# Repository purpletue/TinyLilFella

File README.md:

# TinyLilFella – An Microscopic STM32 Board

### My Tiny Glowing Submission to Hack Club Stardance

---

## Screenshots

*Gotta love them pictures.*

---

## What is this?

An absolutely microscopic (metaphorically... and literally, being under 0.8 cm³) microcontroller board based on the **STM32C071**.

The name is fully deserved. It packs power, an RGB LED, and 6 breakout GPIO lines into a tiny USB dongle form factor!

### Features:

* **STM32C071 Microcontroller** – Arm Cortex-M0+ running up to 48 MHz.
* **Dongle Form Factor** – Plugs straight in like a USB key.
* **Tactile Reset Button** – Dedicated hardware reset driving `NRST` low.
* **Onboard RGB LED** – Connected to PWM-capable pins for status/vibes.
* **10-Pin Header Breakout** – Power rails and 6 general-purpose GPIOs for compact integration.
* **Bootloader button** - The way to program the board.
* **Programmable button** - Just a simple button sitting at PA6, you can program it to do anything!

---

### Repository index:

* root - where [LICENSE](https://github.com/purpletue/TinyLilFella/blob/main/LICENSE) and this document live.
* root/files - where the main files are. like the [project file](https://github.com/purpletue/TinyLilFella/blob/main/files/TinyLilFucker.kicad_pro), [schematic](https://github.com/purpletue/TinyLilFella/blob/main/files/TinyLilFucker.kicad_sch), and [PCB file](https://github.com/purpletue/TinyLilFella/blob/main/files/TinyLilFucker.kicad_pcb) are.
* root/files/production - where the files necessary for production of the PCB are, such as [gerbers.zip](https://github.com/purpletue/TinyLilFella/blob/main/files/production/gerbers.zip) and the [Bill of Materials](https://github.com/purpletue/TinyLilFella/blob/main/files/production/BOM.csv) live.
* root/examples - where code examples such as [LED showcase](https://github.com/purpletue/TinyLilFella/blob/main/examples/led.cpp) are.

## How It Works:

The board takes 5V power directly via standard USB-A / VBUS line. An onboard low-dropout (LDO) regulator steps that down to a clean 3.3V logic level to power the main STM32 MCU and external low-power sensors.

The 10-pin header brings out 6 direct GPIO lines (`PA0` through `PA5`) alongside system ground and power rails for easy modular hooking up.

---

## Why?

Built for **Hack Club Stardance**! I wanted to see how far I could shrink down a functional, highly integrated ARM Cortex dev board into a minimal 1.5 cm³ footprint.

---

## Technical Specifications

| Feature | Details |
| --- | --- |
| **Microcontroller** | STM32C071 (Arm Cortex-M0+, up to 48 MHz) |
| **Form Factor** | Dongle-sized (< 0.8 cm³) |
| **Input Voltage** | 5V via USB-A / VBUS pin |
| **Logic Level** | 3.3V (Onboard LDO regulator) |
| **Pin Count** | 10 pins total (6 GPIO, 2x GND, 1x 3.3V, 1x 5V/VBUS) |
| **Onboard Controls** | Tactile Reset Pushbutton |
| **Indicators** | Onboard RGB LED for programming + an extra power indicator. |

---

## Pinout Mapping

| Pin | Function | Type | Description |
| --- | --- | --- | --- |
| **1** | `GND` | Power | System Ground |
| **2** | `GND` | Power | System Ground |
| **3** | `3V3` | Power | Regulated 3.3V Output |
| **4** | `5V / VBUS` | Power | USB Power Input / 5V Bus |
| **5** | `GPIO 1` | I/O | General Purpose I/O (PA0) |
| **6** | `GPIO 2` | I/O | General Purpose I/O (PA1) |
| **7** | `GPIO 3` | I/O | General Purpose I/O (PA2) |
| **8** | `GPIO 4` | I/O | General Purpose I/O (PA3) |
| **9** | `GPIO 5` | I/O | General Purpose I/O (PA4) |
| **10** | `GPIO 6` | I/O | General Purpose I/O (PA5) |

* Pins PC51 (Blue), PB3 (Green), and PB7 (Red) are used for the onboard LED.

---

## AI Usage Declaration

This project uses AI only in the generation and layout refinement of this `README.md` file.

---

## Contribute

Want to make it better? Open a PR, suggest a feature, or just yell at me on GitHub.

---

## License & Disclaimer

This project is open-source hardware licensed under the **GNU General Public License v3.0 (GPL-3.0)**. Powered 100% by **vibes**. If it breaks, short-circuits, or opens a micro black hole, **that’s on you.**

### just saying,
This project used to be called "TinyLilFucker", so some of the file names keep that name. PLEASE IGNORE IT PLEASE

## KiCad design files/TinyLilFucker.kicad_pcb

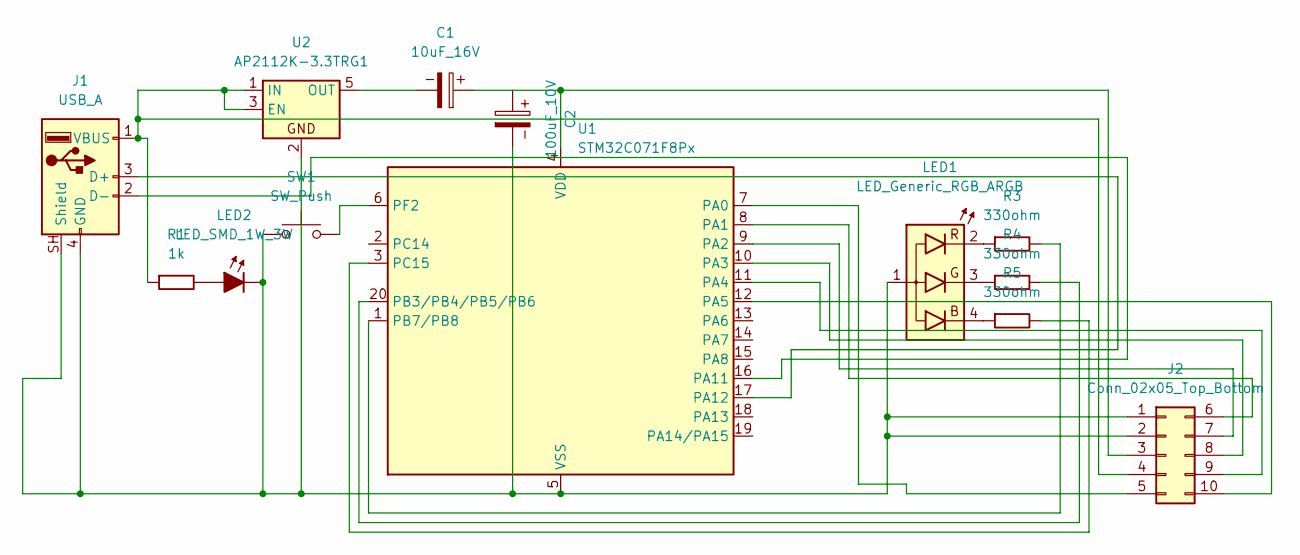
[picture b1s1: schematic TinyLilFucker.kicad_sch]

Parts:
C1: 10uF_16V; C_0805_2012Metric
C2: 100uF_10V; C_0805_2012Metric
J1: USB_A; USB_A_Connfly_DS1098_Horizontal
J2: Conn_02x05_Top_Bottom; PinSocket_2x05_P2.54mm_Vertical_SMD
LED1: LED_Generic_RGB_ARGB; LED_Cree-PLCC4_2x2mm_CW
LED2: LED_SMD_1W_3W; LED_01005_0402Metric
R1: 1k; R_01005_0402Metric
R3, R4, R5: 330ohm; R_0805_2012Metric
SW1: SW_Push; SW_Push_SPST_NO_Alps_SKRK
U1: STM32C071F8Px; TSSOP-20_4.4x6.5mm_P0.65mm
U2: AP2112K-3.3TRG1; SOT-23-5

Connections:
unnamed: J1.3 (D+), U1.17 (PA12)
unnamed: J1.2 (D-), U1.16 (PA11)
unnamed: C2.2, J1.4 (GND), J1.SH (Shield), J2.1, J2.2, LED1.1 (A), LED2.1 (K), SW1.1, U1.5 (VSS), U2.2
unnamed: J1.1 (VBUS), J2.4, R1.1, U2.1 (IN), U2.3 (EN)
unnamed: C1.1, J2.3, U1.4 (VDD)
unnamed: J2.5, U1.7 (PA0)
unnamed: J2.6, U1.8 (PA1)
unnamed: J2.7, U1.9 (PA2)
unnamed: J2.8, U1.10 (PA3)
unnamed: J2.9, U1.11 (PA4)
unnamed: J2.10, U1.12 (PA5)
unnamed: LED1.4 (B), R5.1
unnamed: LED1.3 (G), R4.1
unnamed: LED1.2 (R), R3.1
unnamed: LED2.2 (A), R1.2
unnamed: R4.2, U1.20 (PB3/PB4/PB5/PB6)
unnamed: R3.2, U1.1 (PB7/PB8)
unnamed: R5.2, U1.3 (PC15)
unnamed: SW1.2, U1.6 (PF2)
unnamed: C1.2, U2.5 (OUT)

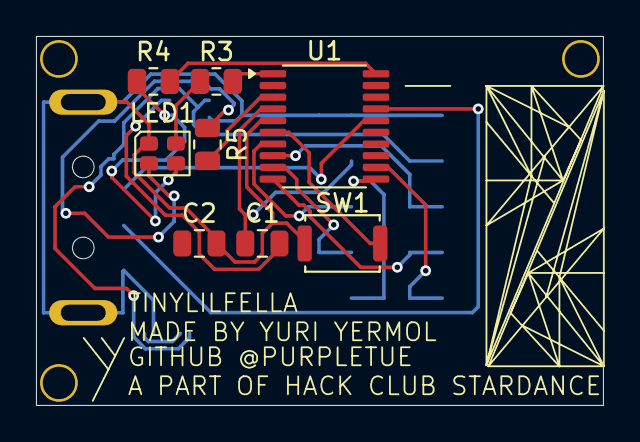
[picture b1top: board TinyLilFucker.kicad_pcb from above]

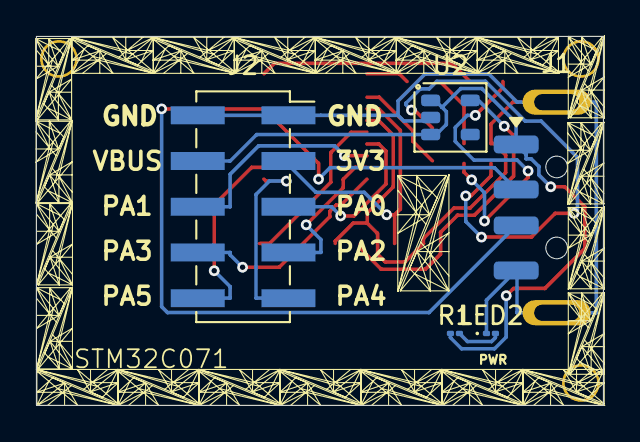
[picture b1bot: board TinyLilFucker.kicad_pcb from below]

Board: 2 copper layers, 31.5 x 20.5 mm, 13 parts (5 on the bottom side), 20 nets.

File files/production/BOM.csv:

"Id";"Designator";"Footprint";"Quantity";"Designation";"Supplier and ref";
1;"C1, C2";"C_0805_2012Metric";2;"";;;
2;"J1";"USB_A_Connfly_DS1098_Horizontal";1;"USB_A";;;
3;"J2";"PinSocket_2x05_P2.54mm_Vertical_SMD";1;"Conn_02x05_Top_Bottom";;;
4;"LED1";"LED_Cree-PLCC4_2x2mm_CW";1;"LED_Generic_RGB_ARGB";;;
5;"R3, R4, R5";"R_0805_2012Metric";3;"330ohm";;;
6;"SW1";"SW_Push_SPST_NO_Alps_SKRK";1;"";;;
7;"U1";"TSSOP-20_4.4x6.5mm_P0.65mm";1;"STM32C071F8Px";;;
8;"U2";"SOT-23-5";1;"AP2112K-3.3TRG1";;;
